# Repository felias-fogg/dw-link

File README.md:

# dw-link 

This Arduino sketch turns your Arduino UNO into a hardware debugger for the classic ATtinys and the ATmegaX8s, such as the ATmega328. It gives you a chance to find out how it feels to use a source-level debugger on an Arduino Uno or an ATtiny board. Do you want to give it a try? Use the *quick-start guide* in the [dw-link manual](https://felias-fogg.github.io/dw-link/) to see if it works for you. 

From version 7 on, the protocol has been changed from [GDB RSP](https://sourceware.org/gdb/current/onlinedocs/gdb.html/Remote-Protocol.html) to a variant of the JTAGICE mkII protocol ([AVR067](https://www.microchip.com/en-us/application-notes/an2587-1)), which implies that you necessarily have to use [PyAvrOCD](https://pyavrocd.io) (version >= 2.0.0) as a GDB server. If you want to connect GDB to dw-link using only the serial line, you need to fall back to version 6.

This repository, which is organized as an Arduino library, contains the following directories:

* [**src**](src/) contains an empty header file so that it fits the format of a library,
* [**examples**](examples/) contains 
  * the [dw-link](examples/dw-link/) sketch, the debugger firmware, and 
  * the [testprobe](examples/testprobe/) sketch, which can be used to run tests on a freshly assembled dw-link probe shield,
* [**docs**](docs/) contains the documentation files for the [manual](https://felias-fogg.github.io/dw-link/),
* [**extras**](extras/) contains the folder [pcb](extras/pcb/) with design data (KiCad) for the optional dw-link probe.

<sup><sub>The cover picture was designed based on vector graphics by [captainvector at 123RF](https://de.123rf.com/profile_captainvector).</sub></sup>

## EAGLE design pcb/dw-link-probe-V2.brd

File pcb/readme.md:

# The *dw-link probe*: Hardware for dw-link

<br />This work is licensed under a <a rel="license" href="http://creativecommons.org/licenses/by/4.0/">Creative Commons Attribution 4.0 International License</a>.

When you want to debug your projects using dw-link more than once, it is a good idea to have a hardware solution. For instance, an Arduino shield. As described in the manual, you can just assemble a solution on a prototype board, which works for 5 V projects with less than 20 mA of supply current. 

The current design of the *dw-link probe* is more ambitious, but far from an industrial-strength hardware debugging tool as, e.g., Atmel ICE. The limitations for the target boards are:

* 3.3 to 5 V supply voltage (but not lower),
* reasonable loads on the SPI lines, e.g., an LED and a 1 kΩ series resistor (but no stronger resistor),
* no capacitive load on the RESET line of the target,
* no loads higher than a 10 kΩ resistance on the RESET line,
* minimum target MCU clock frequency of 4 kHz.

If these constraints are met, the dw-link probe should work.  Otherwise, one might encounter strange behavior and/or error messages. 

The current version (V3.1) of the dw-link probe (an Arduino UNO shield) uses mainly THT components, which should make it easy to assemble it using [these instructions](assembly.md). The three SMD components can also be hand-soldered to the PCB since the solder pads are extra large. 

**Note:** It is advisable to solder an additional 100 µF or more capacitor between 5V and GND. Otherwise, the hardware debugger might brown out when power-cycling the target, and you will need to disconnect and reconnect.

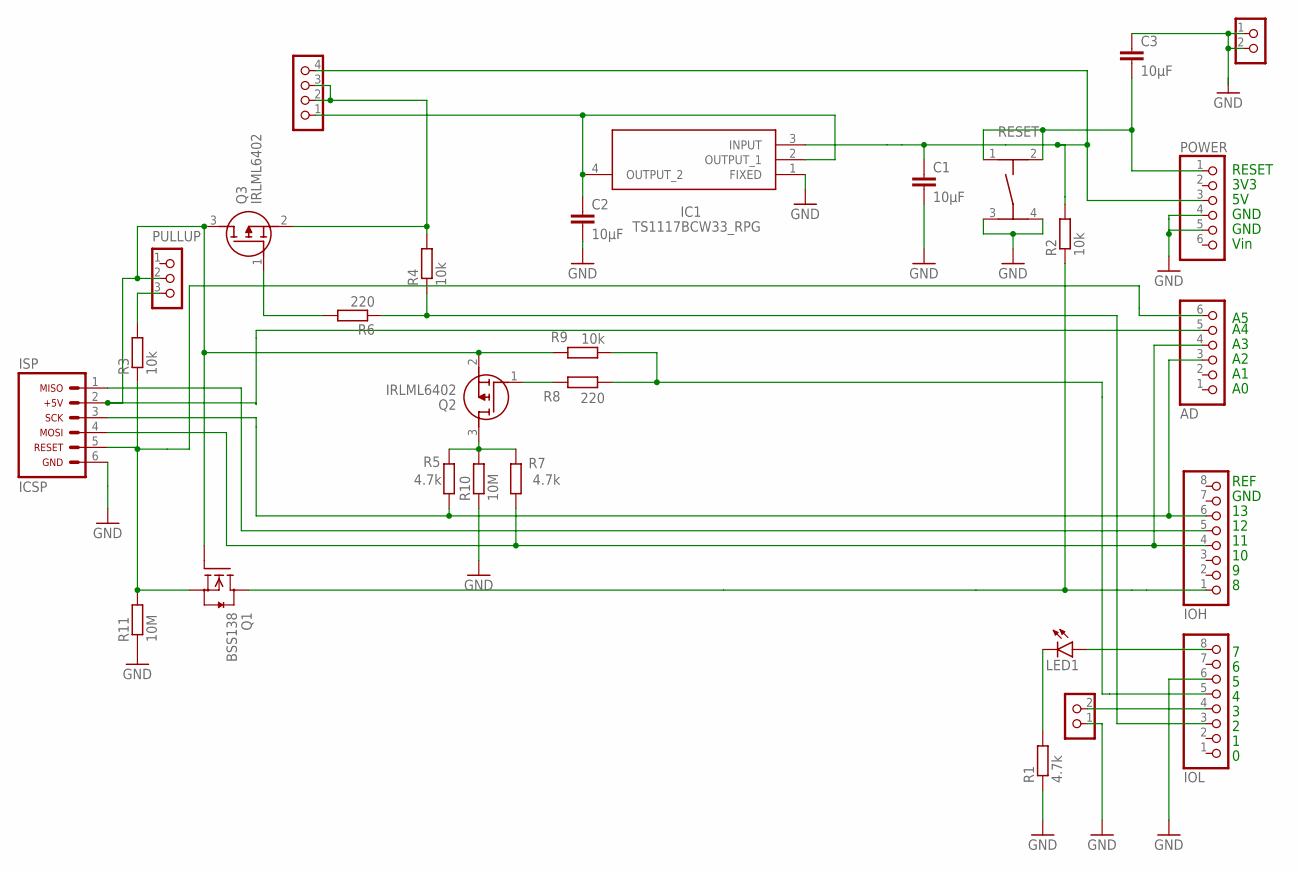
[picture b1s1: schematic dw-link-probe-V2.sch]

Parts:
AD: PINHD-1X6; 1X06
C1, C2, C3: 10µF; C1206
DEBUG: CON_HEADER_1X02-PTH; M1X2
IC1: TS1117BCW33_RPG; SOT230P700X190-4N
IOH: PINHD-1X8; 1X08
IOL: PINHD-1X8; 1X08
ISP: ARDUINO_CONN-ICSP; CONN-2X03
LED1: LEDCHIPLED_1206; CHIPLED_1206
POWER: PINHD-1X6; 1X06
PULLUP: CON_HEADER_1X03-PTH; M1X3
Q1: BSS138; SOT23
Q2, Q3: IRLML6402; SOT95P237X112-3N
R1, R5, R7: 4.7k; R1206
R2, R3, R4, R9: 10k; R1206
R6, R8: 220; R1206
R10, R11: 10M; R1206
RESDIS: CON_HEADER_1X02-PTH; M1X2
RESET: TASTER-9314_SMD
SUPPLY: CON_HEADER_1X04; M1X4

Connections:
GND: C1.2, C2.2, C3.1, DEBUG.1, IC1.1 (FIXED), IOL.6, ISP.6, POWER.4, POWER.5, R1.1, R10.1, R11.1, RESDIS.1, RESDIS.2, RESET.3, RESET.4
unnamed: C1.1, IC1.3 (INPUT), POWER.3, R2.2, SUPPLY.4
unnamed: IOH.1, Q1.3 (D), R2.1
unnamed: AD.6, ISP.5, Q1.2 (S), R3.1, R11.2
unnamed: IOL.3, R4.1, R6.1
unnamed: Q3.1 (G), R6.2
unnamed: AD.5, ISP.2, PULLUP.2, Q1.1 (G), Q2.2 (S), Q3.3 (D), R9.2
unnamed: Q2.1 (G), R8.2
unnamed: IOL.8, LED1.A
unnamed: PULLUP.3, R3.2
unnamed: IOH.5, ISP.1
unnamed: AD.3, IOH.6, ISP.3, R5.1
unnamed: AD.4, IOH.4, ISP.4, R7.1
unnamed: Q3.2 (S), R4.2, SUPPLY.2, SUPPLY.3
unnamed: C2.1, IC1.2 (OUTPUT_1), IC1.4 (OUTPUT_2), SUPPLY.1
unnamed: Q2.3 (D), R5.2, R7.2, R10.2
unnamed: IOL.5, R8.1, R9.1
unnamed: DEBUG.2, IOL.4
unnamed: C3.2, POWER.1, RESET.1, RESET.2
unnamed: LED1.C, R1.2

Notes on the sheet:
GND
REF
RESET
3V3
Vin

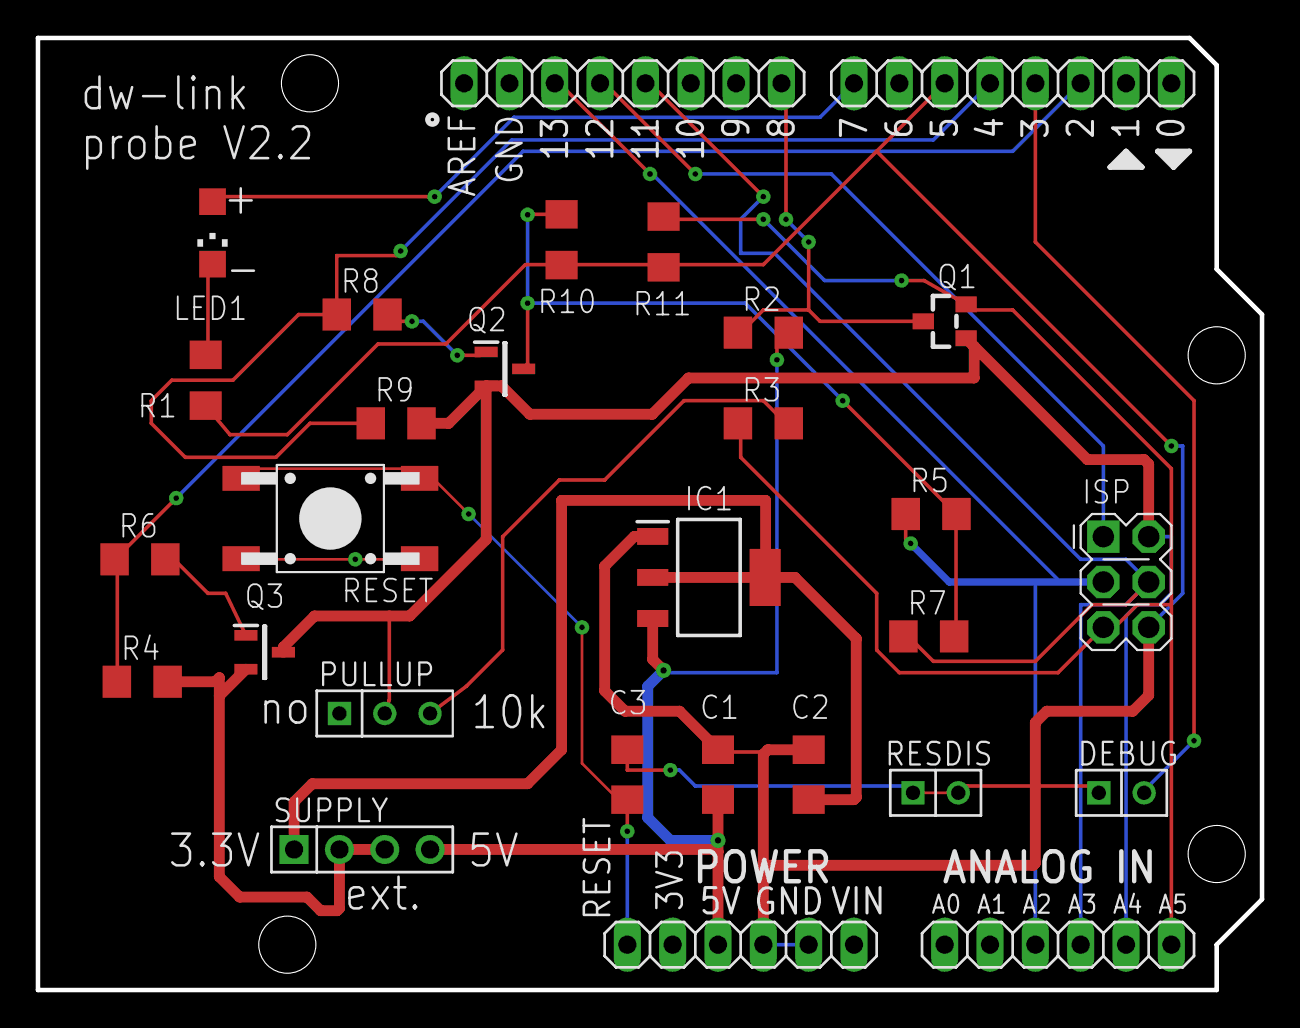
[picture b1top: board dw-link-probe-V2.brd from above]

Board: 2 copper layers, 68.6 x 53.3 mm, 29 parts (0 on the bottom side), 20 nets.

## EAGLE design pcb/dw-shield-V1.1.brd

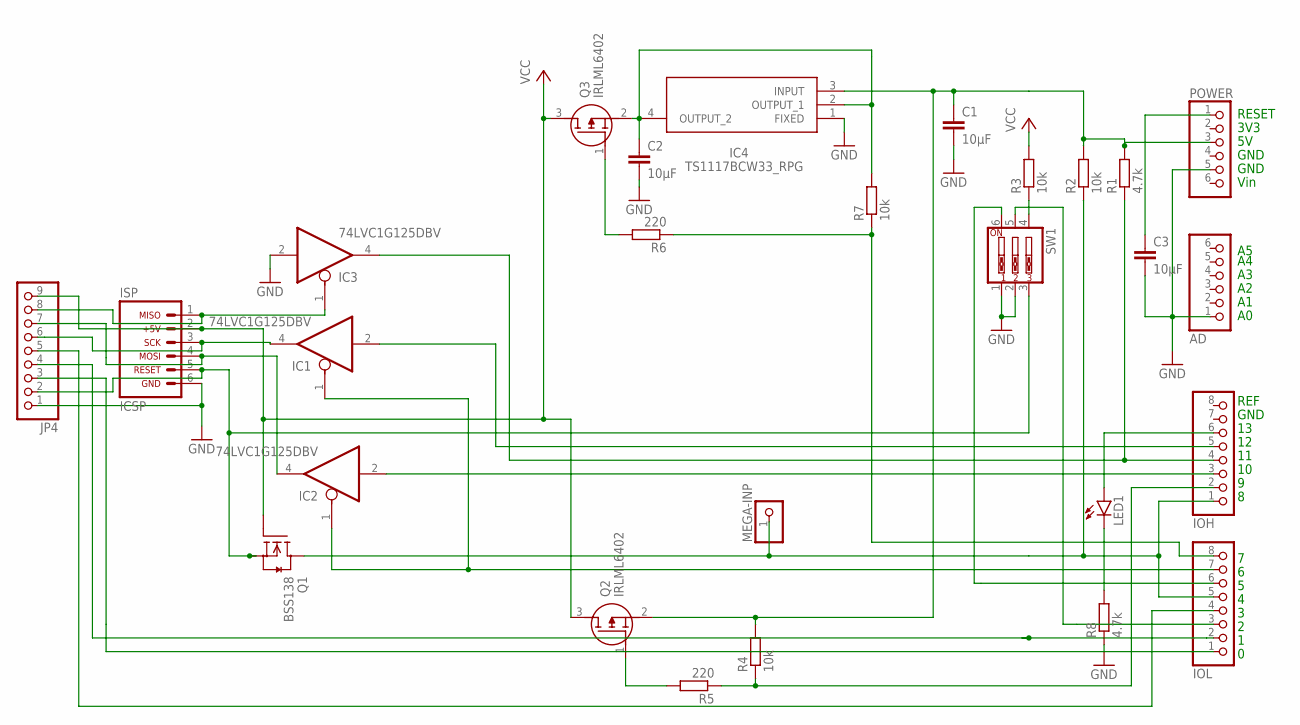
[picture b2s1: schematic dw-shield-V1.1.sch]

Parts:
AD: PINHD-1X6; 1X06
C1, C2, C3: 10µF; C1206
IC1, IC2, IC3: 74LVC1G125DBV; SOT23-5
IC4: TS1117BCW33_RPG; SOT230P700X190-4N
IOH: PINHD-1X8; 1X08
IOL: PINHD-1X8; 1X08
ISP: ARDUINO_CONN-ICSP; CONN-2X03
JP4: PINHD-1X9; 1X09
LED1: LEDCHIPLED_1206; CHIPLED_1206
MEGA-INP: PINHD-1X1; 1X01
POWER: PINHD-1X6; 1X06
Q1: BSS138; SOT23
Q2, Q3: IRLML6402; SOT95P237X112-3N
R1, R8: 4.7k; R1206
R2, R3, R4, R7: 10k; R1206
R5, R6: 220; R1206
SW1: SW_DIP-3; EDG-03

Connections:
GND: AD.1, C1.2, C2.2, C3.2, IC1.3 (GND), IC2.3 (GND), IC3.2 (I), IC3.3 (GND), IC4.1 (FIXED), ISP.6, JP4.1, POWER.5, R8.1, SW1.1, SW1.2
unnamed: C1.1, IC4.3 (INPUT), POWER.3, Q2.2 (S), R1.2, R2.2, R4.2
unnamed: IOH.1, IOL.5, MEGA-INP.1, Q1.3 (D), R2.1
unnamed: IC1.4 (O), ISP.3, JP4.6
unnamed: IC3.1 (OE), ISP.1, JP4.8
unnamed: IC2.4 (O), ISP.4, JP4.7
unnamed: IC1.1 (OE), IC2.1 (OE), IOL.7
unnamed: IC2.2 (I), IOH.3
unnamed: IC1.2 (I), IOH.5
unnamed: IC3.4 (O), IOH.4, R1.1
unnamed: Q2.1 (G), R5.2
unnamed: ISP.5, JP4.2, Q1.2 (S), SW1.3
unnamed: R3.1, SW1.4
unnamed: IOL.6, SW1.6
unnamed: IOL.3, SW1.5
unnamed: C2.1, IC4.2 (OUTPUT_1), IC4.4 (OUTPUT_2), Q3.2 (S), R7.2
unnamed: IOH.2, R4.1, R5.1
unnamed: Q3.1 (G), R6.2
unnamed: IOL.8, R6.1, R7.1
unnamed: C3.1, POWER.1
unnamed: IOL.2, JP4.4
unnamed: IOH.6, LED1.A
unnamed: LED1.C, R8.2
unnamed: IOL.1, JP4.3
unnamed: IOL.4, JP4.5
VCC: IC1.5 (VCC), IC2.5 (VCC), IC3.5 (VCC), ISP.2, JP4.9, Q1.1 (G), Q2.3 (D), Q3.3 (D), R3.2

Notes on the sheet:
GND
REF
RESET
3V3
Vin

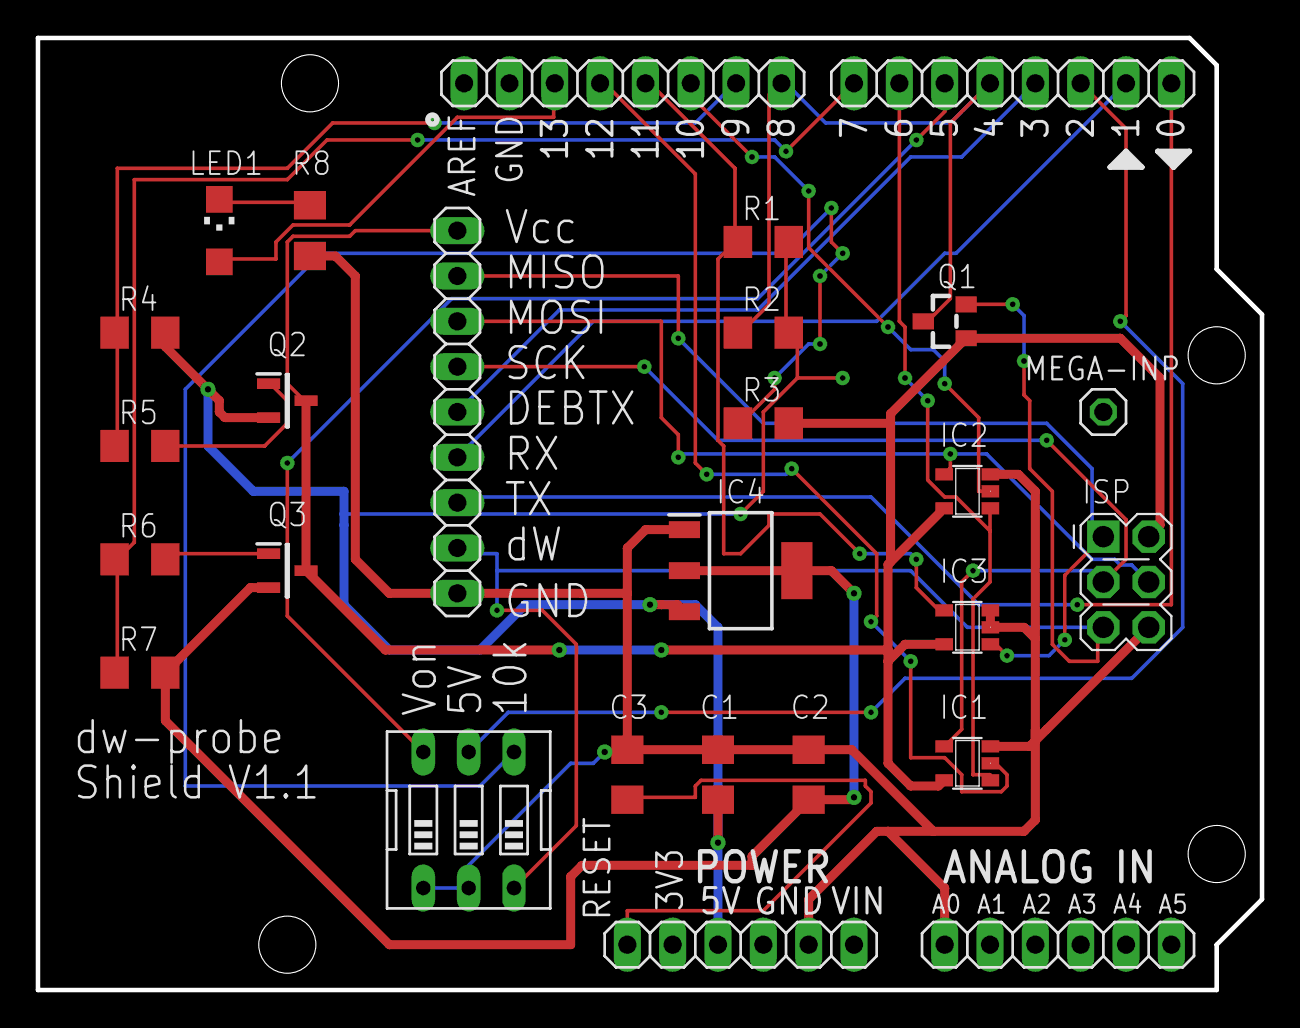
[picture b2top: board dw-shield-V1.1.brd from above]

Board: 2 copper layers, 68.6 x 53.3 mm, 27 parts (0 on the bottom side), 26 nets.

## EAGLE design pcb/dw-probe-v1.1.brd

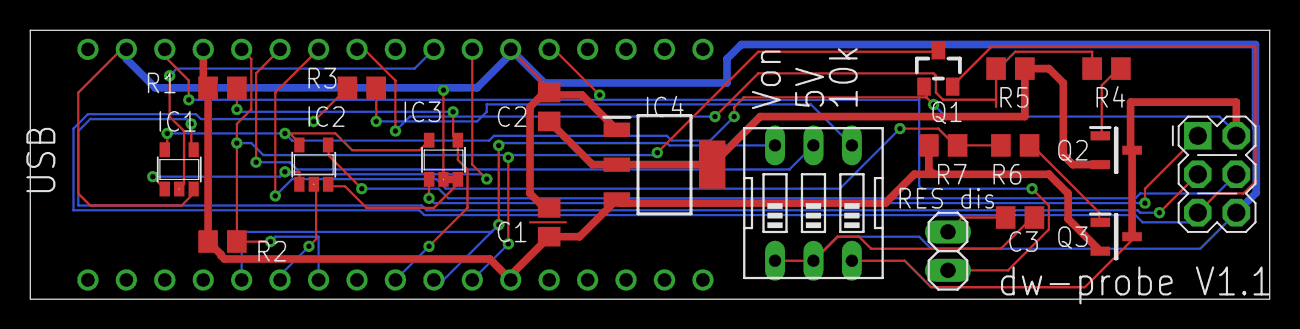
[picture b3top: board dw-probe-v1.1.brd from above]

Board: 2 copper layers, 81.9 x 17.8 mm, 21 parts (0 on the bottom side), 22 nets.

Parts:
C1, C2, C3: 10uF; C0805
IC1, IC2, IC3: 74LVC1G125DBV; SOT23-5
IC4: TS1117BCW33_RPG; SOT230P700X190-4N
JP1: CONN-2X03
Q1: BSS138; SOT23
Q2, Q3: IRLML6402; SOT95P237X112-3N
R1: 4.7k; R0805
R2, R3, R5, R7: 10k; R0805
R4, R6: 220; R0805
RSTDIS: 1X02
SW1: EDG-03
U$1: ARDUINO_MICROFOOTPRINT; ARDUINO-MICRO

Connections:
GND: C1.2, C2.2, C3.2, IC1.3, IC2.3, IC3.2, IC3.3, IC4.1, JP1.6, SW1.1, SW1.2, U$1.D11, U$1.GND
unnamed: R3.2, SW1.4
unnamed: SW1.6, U$1.A1, U$1.NC8
unnamed: IC1.1, IC2.1, U$1.D2
unnamed: C1.1, IC4.3, Q3.2, R1.2, R2.2, R7.1, U$1.5V, U$1.D9
unnamed: IC1.2, U$1.D3
unnamed: IC2.2, U$1.A2
unnamed: IC3.4, R1.1, U$1.A5
unnamed: RSTDIS.2, U$1.D10, U$1.RST
unnamed: IC2.4, JP1.4
unnamed: SW1.5, U$1.D7
unnamed: IC3.1, JP1.1
unnamed: C3.1, RSTDIS.1
unnamed: JP1.5, Q1.2, R3.1
unnamed: Q3.1, R6.1
unnamed: C2.1, IC4.2, IC4.4, Q2.2, R5.2
unnamed: IC1.4, JP1.3
unnamed: R4.1, R5.1, U$1.D5
unnamed: Q2.1, R4.2
unnamed: R6.2, R7.2, U$1.D6
unnamed: Q1.3, R2.1, U$1.A3, U$1.D8, U$1.NC7
VCC: IC1.5, IC2.5, IC3.5, JP1.2, Q1.1, Q2.3, Q3.3, SW1.3

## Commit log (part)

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2021-11-24 V 1.0.2 - without build files
2021-11-30 V1.0.3
2021-12-02 V1.0.4
2021-12-04 V1.0.5
2021-12-07 V1.0.6
2021-12-10 V1.0.7
2021-12-11 V1.0.8
2021-12-20 V1.0.9
2021-12-27 V1.1.0
2021-12-29 V1.1.1
2021-12-30 V1.1.2
2021-12-30 V1.1.3
2021-12-31 V1.1.4 - public release
2021-12-31 changelog updated
2021-12-31 readme updated
2021-12-31 added workflow
2021-12-31 corrected workflow
2021-12-31 V1.1.5
2022-01-03 V1.1.6
2022-01-03 V1.1.6 - missing pic
2022-01-03 V1.1.6 - workflow change
2022-01-03 V1.1.6 - unit tests removed
2022-01-03 V1.1.6 - workflow changed
2022-01-04 V1.1.7
2022-01-04 V1.1.8
2022-01-05 V1.1.9
2022-01-05 V1.1.9 - updated docu
2022-01-05 V1.1.10
2022-01-06 manual update
2022-01-08 update pcb and doc
2022-01-08 blockusb branch
2022-01-09 V1.1.11
2022-01-09 pic update
2022-01-09 updated workflow
2022-01-11 V1.1.12
2022-01-11 V1.1.12 - dwlink nano fix
2022-01-15 V1.2.0
2022-01-15 V1.2.0.a
2022-01-15 V1.2.1
2022-01-15 V1.2.2
2022-01-17 V1.2.3
2022-01-17 V1.2.4
2022-01-17 manual - wiring fix
2022-01-19 V1.2.5
2022-01-19 V1.2.5 - workflow
2022-01-19 V1.3.0
2022-01-20 V1.3.1
2022-01-20 V1.3.2
2022-01-20 V1.3.3
2022-01-22 V1.3.4
2022-01-23 V1.3.5
2022-01-26 V1.3.6
2022-02-02 V1.3.7
2022-02-02 optimized PDF file
2022-02-02 V1.3.7 (updated)
2022-02-02 V1.3.7 (manual updated)
2022-02-04 V1.3.8
2022-02-17 V1.3.9
2022-03-12 platformio debugging calls 'mo dwconnect'
2022-03-12 V1.3.10
2022-03-13 Changed gitignore
2022-11-24 Disable pull up on TMOSI upon disableSpiPins()
2023-01-07 Added symbolic link from src to dw-link to make platformio build possible
2023-08-11 V2.0.0
2023-08-11 fixed some inconsistencies
2023-08-15 V2.1.0
2023-08-15 V2.1.2
2023-08-15 V2.1.2 (incl. documentation)
2023-08-16 V2.1.3
2023-08-16 V2.1.4
2023-08-17 V2.1.5
2023-08-18 V 2.1.6
2023-08-20 V2.1.7
2023-08-21 V2.1.8
2023-08-22 dw-server and documentation
2023-08-22 fixed typos in quickstart
2023-08-22 readme fixes
2023-08-22 quzickstart fixes
2023-08-23 added checks to quickstart
2023-08-23 V2.1.9
2023-08-23 readme fix
2023-08-24 docu update
2023-08-24 workflow update
2023-08-26 changelog ficed
2023-08-26 Revert "workflow update"
    This reverts commit 78d8907c8fad9df0ea710d77213ca2aa1fff75bf.
2023-08-26 re-apply workflow changes
2023-08-27 docu extended
2023-08-27 pcb fix
2023-08-27 .gitignore removed from repo
2023-08-27 V2.2.0
2023-08-27 V2.2.1
2023-08-28 V2.3.0
2023-08-28 V3.0.0
2023-08-28 changelog
2023-08-28 manual fix
2023-08-28 .gitignore
2023-08-29 V3.0.1
2023-08-29 quickstart pdf
2023-08-29 quickstart update
2023-08-29 Manual and Quickstart fixes
2023-08-29 Quickstart fixes
2023-08-29 quickstart
2023-09-05 V3.1.0
2023-09-06 V3.1.1
2023-09-06 readme
2023-09-06 docs
2023-09-09 PCB & docu
2023-09-10 documentation update
2023-09-11 assembly update
2023-09-11 V3.3.0
2023-09-11 changelog fix
2023-09-11 CS2 fix
2023-09-12 V3.4.0
2023-09-13 low frequency
2023-09-13 V3.5.0
2023-09-13 V3.5.1
2023-09-15 V3.5.2
2023-09-18 testprobe
2023-09-20 new dw-link probe V3.1
2023-09-20 new example, restored pics
2023-09-21 description of debugging UNO with serial connection
2023-09-21 adapted to new gede version
2023-09-22 manual toubleshooting: ISP programmer failure
2023-09-23 V3.5.3
2023-09-23 going back to my version of gede
2023-09-25 readme update
2023-10-05 manual
2023-12-18 documentation adapted, in particular new schemativ for probe
2024-02-25 V3.5.4
2024-12-16 V3.5.5
2024-12-16 quickstart.pdf update
2024-12-17 V3.5.6
2024-12-23 V4.0.0 - with Arduino IDE 2.0 support
2024-12-28 V4.0.0
2024-12-29 all tool files ready to roll
2024-12-29 tools files moved to felias-fogg.github.io
2024-12-30 added quickstart link
2024-12-30 edited quickstarts
2024-12-31 core mods adapted, MiniCore works
2024-12-31 readme updates + core-mods fixes
2025-01-01 V4.0.1
2025-01-02 V4.0.2
2025-01-02 update manual
2025-01-06 V4.0.3
2025-01-06 updated docs + dw-server for Linux
2025-01-07 assembly notes adapted and testprobe.ino extended
2025-01-07 quickstart hardlink
2025-01-07 update doc because of windows hickup
2025-01-08 doc update and Windows tool issue mitigation
2025-01-08 doc update
2025-01-16 V4.0.4
2025-01-18 V4.1.0
2025-01-19 V4.2.0
2025-01-19 update changelog
2025-02-01 V4.3.0
2025-02-01 V4.3.1
2025-02-10 V4.4.0
2025-02-14 manual V4.4.0
2025-02-26 V4.5.0
2025-03-27 V5.0.0-pre1
2025-03-28 v5.0.0-pre2
2025-04-16 v5.0.0
2025-04-17 v5.1.0
2025-07-22 v5.2.0
2025-07-29 ISPMON removed
2025-07-30 v5.2.1
2025-07-31 v5.2.2
2025-08-01 v5.2.3
2025-08-18 v5.2.4
2025-09-26 Deployed 45a31e7 with MkDocs version: 1.6.1
2025-09-26 mkdocs
2025-09-26 Deployed 1673c36 with MkDocs version: 1.6.1
2025-09-26 Deployed 426f6d8 with MkDocs version: 1.6.1
2025-10-04 Deployed e834845 with MkDocs version: 1.6.1
2025-10-04 Deployed f349ee1 with MkDocs version: 1.6.1
2025-11-23 Deployed 1fbc1d6 with MkDocs version: 1.6.1
2025-12-07 v5.3.0
2025-12-07 Deployed f28f431 with MkDocs version: 1.6.1
2025-12-13 v5.4.0
2025-12-16 Deployed 3473d8e with MkDocs version: 1.6.1
2025-12-16 Deployed e3ad75b with MkDocs version: 1.6.1
2025-12-17 v6.0.0
2025-12-17 v6.0.1
2025-12-17 workflof: exclude nano
2025-12-17 workflow: exclude nano
2025-12-17 Deployed 749f7cd with MkDocs version: 1.6.1
2025-12-27 dw-uploader
2025-12-27 monitor commands adapted to PyAvrOCD conventions
2025-12-27 new build workflow
2025-12-27 workflow
2025-12-28 workflow for dw-uploader ready
2025-12-28 workflow fix
2025-12-28 v6.0.2
2025-12-28 workflow and pyintstaller fix
2025-12-28 docs fw-upload
2025-12-28 Deployed 1be1a03 with MkDocs version: 1.6.1
2025-12-30 v6.0.3
2025-12-30 v6.0.3 docs
2025-12-30 Deployed 85ff878 with MkDocs version: 1.6.1
2026-01-26 v6.1.0
2026-01-31 Deployed 478c51d with MkDocs version: 1.6.1
2026-01-31 no modw
2026-02-15 Deployed 124e81a with MkDocs version: 1.6.1
2026-02-15 typos, .gitignore, and dw-uploader
2026-04-07 replace ATTinyCore by TinyCore in docs
2026-04-07 Deployed 86a4c79 with MkDocs version: 1.6.1
2026-04-07 docs update
2026-04-07 Deployed ea6e4c1 with MkDocs version: 1.6.1
2026-04-07 Deployed f506cd0 with MkDocs version: 1.6.1
2026-04-11 Deployed ea6aefb with MkDocs version: 1.6.1

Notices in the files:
README.md:
License: GPL v3
License: CCBY4.0
parts and their libraries:
m-pad-2.1: License : GNU General Public License version 2 (see bottom)
